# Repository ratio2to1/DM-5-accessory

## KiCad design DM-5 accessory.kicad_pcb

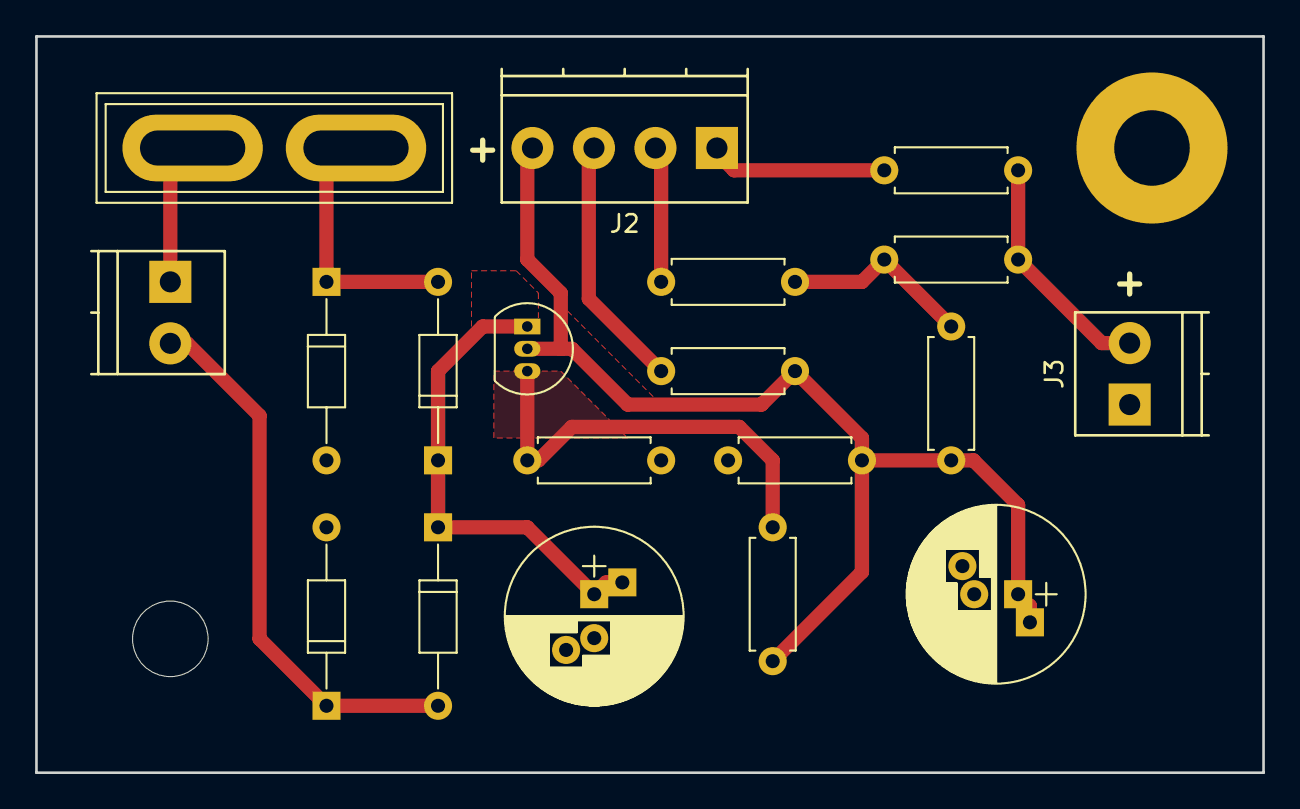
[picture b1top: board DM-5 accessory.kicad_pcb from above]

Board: 2 copper layers, 69.8 x 41.9 mm, 19 parts (0 on the bottom side), 12 nets.

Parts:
1N4148: D; D_DO-35_SOD27_P10.16mm_Horizontal
C1: 10.0 uF 63V; CP_Radial_D10.0mm_P2.50mm_P5.00mm
C2: 1.0 uF 63V; CP_Radial_D10.0mm_P2.50mm_P5.00mm
D: 1N4148; D_DO-35_SOD27_P10.16mm_Horizontal
D3, D4: D; D_DO-35_SOD27_P10.16mm_Horizontal
F1: 1A ATC; BladeFuse-CarType
J1: 24VAC; TerminalBlock_Pheonix_PT-3.5mm_2pol
J2: Input; TerminalBlock_Pheonix_PT-3.5mm_4pol
J3: Output; TerminalBlock_Pheonix_PT-3.5mm_2pol
R1, R2, R4, R6: 20K; R_Axial_DIN0207_L6.3mm_D2.5mm_P7.62mm_Horizontal
R3, R5: 10K; R_Axial_DIN0207_L6.3mm_D2.5mm_P7.62mm_Horizontal
R7: 1K2; R_Axial_DIN0207_L6.3mm_D2.5mm_P7.62mm_Horizontal
R8: 8K8; R_Axial_DIN0207_L6.3mm_D2.5mm_P7.62mm_Horizontal
U1: LR8; TO-92_Inline_Narrow_Oval

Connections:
unnamed: 1N4148.1, C1.1, D3.1, U1.1
unnamed: C1.2, C2.2, D.2, D4.2, J3.1, R2.2, R7.1
unnamed: C2.1, J2.4, R1.2, R2.1, R3.2, R8.2, U1.2
unnamed: 1N4148.2, D.1, F1.2
unnamed: D3.2, D4.1, J1.2
unnamed: F1.1, J1.1
unnamed: J2.1, R6.1
unnamed: J2.2, R4.1
unnamed: J2.3, R1.1
unnamed: J3.2, R5.1, R6.2
unnamed: R3.1, R4.2, R5.2
unnamed: R7.2, R8.1, U1.3

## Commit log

2017-12-01 added, I think
2017-12-02 respin
    better foorprints, single sided board
2017-12-04 respin
    swap LR645 -> LR8
